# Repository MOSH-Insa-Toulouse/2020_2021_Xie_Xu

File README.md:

# 2020_2021- Qiang XU and Xiaotong XIE in 5ISS 

<div align=center></div>

Our class in SMART DEVICES

Contact : [Qiang XU](qxu@etud.insa-toulouse.fr)
          [Xiaotong XIE](x_xie@etud.insa-toulouse.fr)

- [x] Introduction the measurement chain and smart devices
- [x] Internship at AIME
- [x] TPs relating to the design of an analog circuit to interface the gas sensor produced to the AIME
- [x] TP on Git and the GitHub platform
- [x] TP on microcontrollers and open source hardware
- [x] TP on the production of electronic cards under KiCad
- [ ] Complete the whole project
---

## 2020_2021 5ISS KiCad

### Arduino Project

### KiCad - Shield for Arduino

#### TODO Concevoir une carte avec KiCad

- [x] Create project
- [x] Try to make the initial connection
- [x] Design the circuit board
- [x] Create original AIME components
- [x] Import 3D models
- [x] Complete package
- [x] Complete circuit wiring
- [ ] Solve the problem that the circuit board cannot display normally
- [x] Practice using Github
- [ ] Use Github proficiently

#### KiCad Tools used

[KiCad EDA - Schematic Capture & PCB Design Software](https://kicad-pcb.org/), version: 5.1.8

Open source EDA / electronics CAD software for Windows, macOS and Linux.

[Find 3D mod as you want!](https://grabcad.com/library)

If you want, you can place a tractor or Trump model on the circuit board

[Library of kicad](https://gitlab.com/kicad/libraries)

#### Librairies de composants

* LED_THT:LED_D5.0mm
* Resistor_THT:R_Axial_DIN0207_L6.3mm_D2.5mm_P10.16mm_Horizontal
* MyAIME:SIP-8
* Capacitor_THT:C_Radial_D4.0mm_H5.0mm_P1.50mm
* Package_DIP:DIP-8_W7.62mm
* MyAIME:TO-5-10_Window

#### Electrical diagram

## Component placement

## Routage

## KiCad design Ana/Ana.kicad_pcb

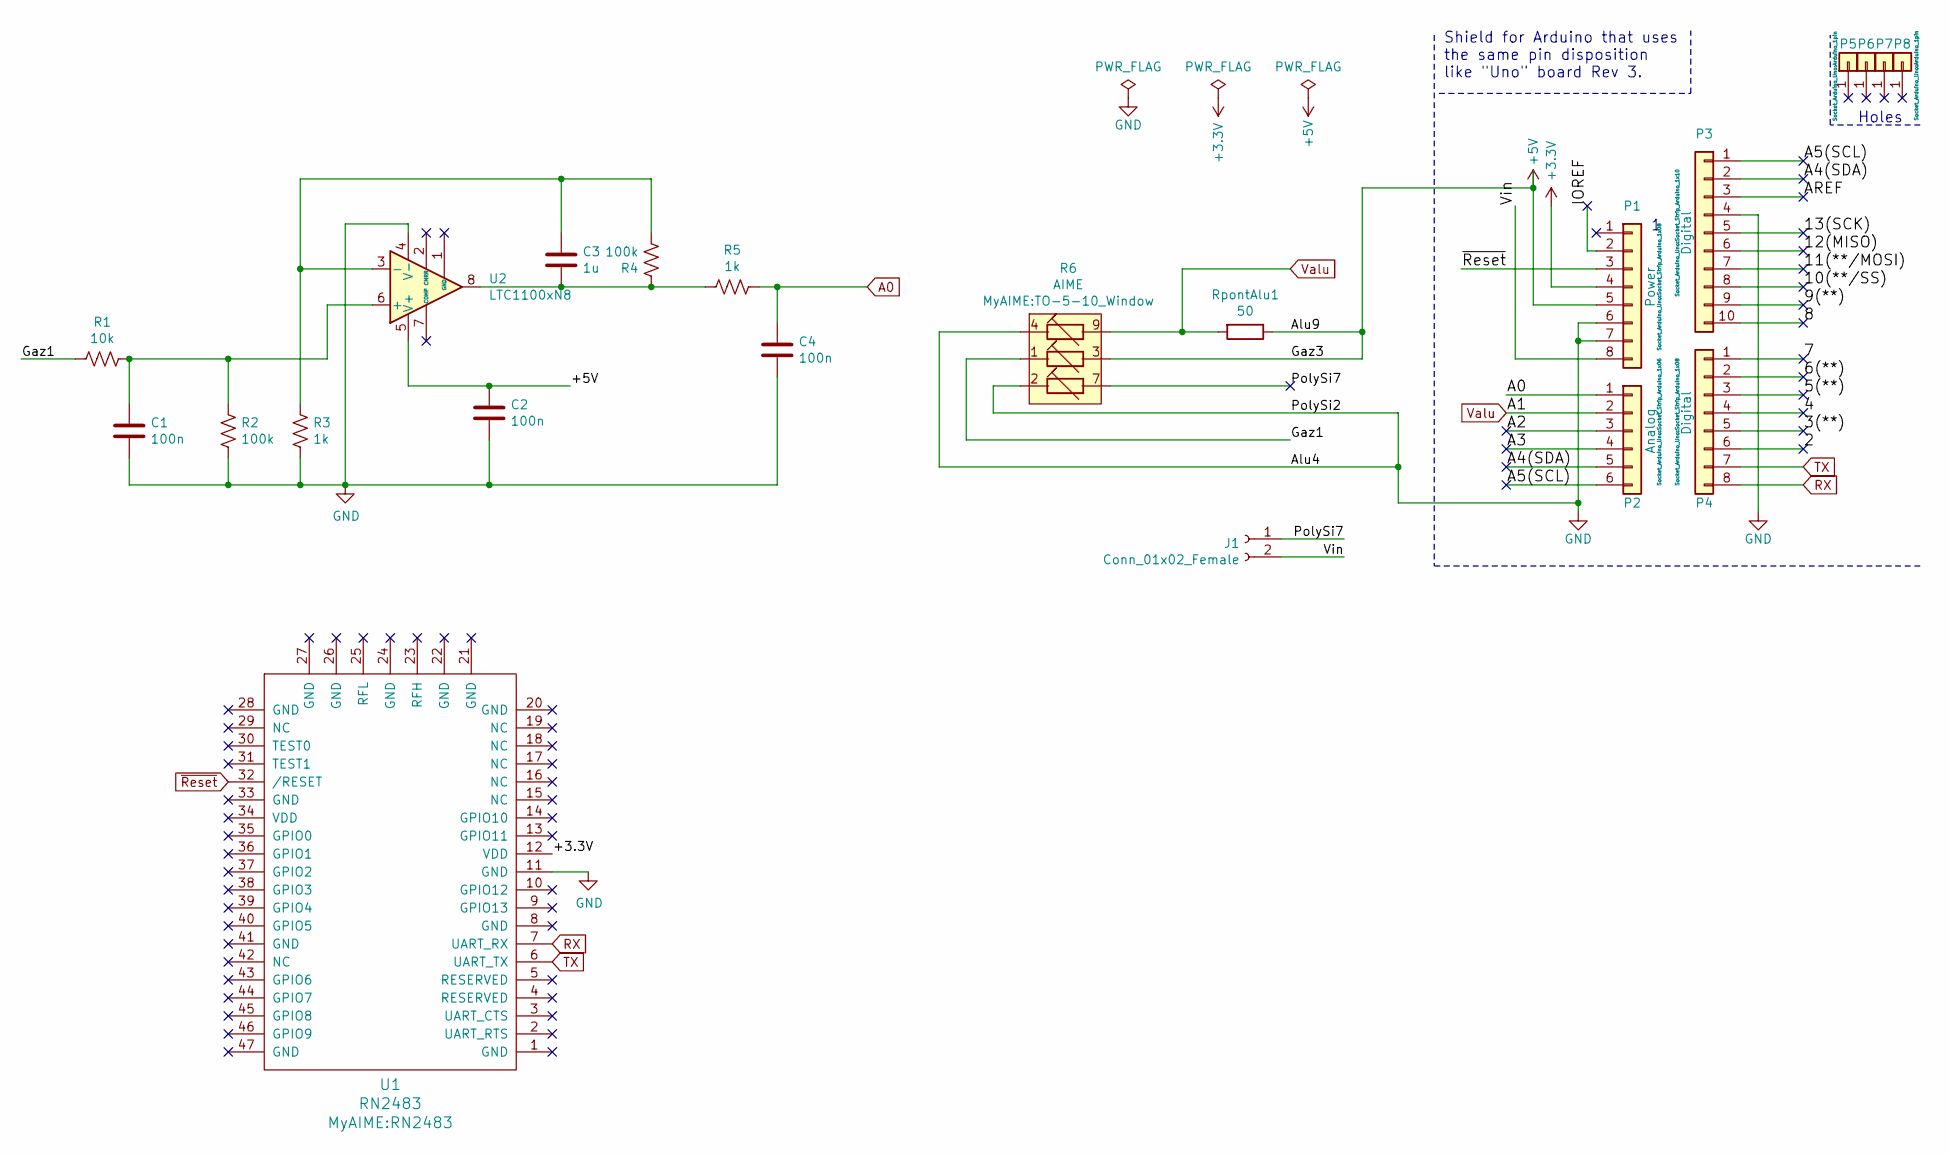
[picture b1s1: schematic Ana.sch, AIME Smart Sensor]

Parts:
C1, C2, C4: 100n; C_Radial_D4.0mm_H5.0mm_P1.50mm
C3: 1u; C_Radial_D4.0mm_H5.0mm_P1.50mm
J1: Conn_01x02_Female; PinSocket_1x02_P1.27mm_Vertical
P1: Power; Socket_Strip_Arduino_1x08
P2: Analog; Socket_Strip_Arduino_1x06
P3: Digital; Socket_Strip_Arduino_1x10
P4: Digital; Socket_Strip_Arduino_1x08
P5, P6, P7, P8: CONN_01X01; Arduino_1pin
R1: 10k; R_Axial_DIN0207_L6.3mm_D2.5mm_P10.16mm_Horizontal
R2, R4: 100k; R_Axial_DIN0207_L6.3mm_D2.5mm_P10.16mm_Horizontal
R3, R5: 1k; R_Axial_DIN0207_L6.3mm_D2.5mm_P10.16mm_Horizontal
R6: AIME; TO-5-10_Window
RpontAlu1: 50; R_Axial_DIN0207_L6.3mm_D2.5mm_P10.16mm_Horizontal
U1: RN2483
U2: LTC1100xN8; DIP-8_W7.62mm

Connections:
+3V3: P1.4
+5V: C2.1, P1.5, R6.3, RpontAlu1.1, U2.5 (V+)
/2: P4.6
/3(**): P4.5
/4: P4.4
/5(**): P4.3
/6(**): P4.2
/7: P4.1
/8: P3.10
/9(**): P3.9
/10(**/SS): P3.8
/11(**/MOSI): P3.7
/12(MISO): P3.6
/13(SCK): P3.5
/+3.3V: U1.12 (VDD)
/A2: P2.3
/A3: P2.4
/A4(SDA): P2.5, P3.2
/A5(SCL): P2.6, P3.1
/AREF: P3.3
/Gaz1: R1.1, R6.1
/IOREF: P1.2
/PolySi7: J1.1, R6.7
/Vin: J1.2, P1.8
A0: C4.1, P2.1, R5.1
GND: C1.2, C2.2, C4.2, P1.6, P1.7, P3.4, R2.1, R3.1, R6.2, R6.4, U1.11 (GND), U2.4 (V-)
unnamed: C1.1, R1.2, R2.2, U2.6 (+)
unnamed: C3.1, R3.2, R4.2, U2.3 (-)
unnamed: C3.2, R4.1, R5.2, U2.8
RX: P4.8, U1.7 (UART_RX)
TX: P4.7, U1.6 (UART_TX)
Valu: P2.2, R6.9, RpontAlu1.2
~Reset: P1.3, U1.32 (/RESET)

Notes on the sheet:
Holes
Shield for Arduino that uses the same pin disposition like "Uno" board Rev 3.

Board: 2 copper layers, 22 parts (0 on the bottom side), 15 nets, no tracks yet.

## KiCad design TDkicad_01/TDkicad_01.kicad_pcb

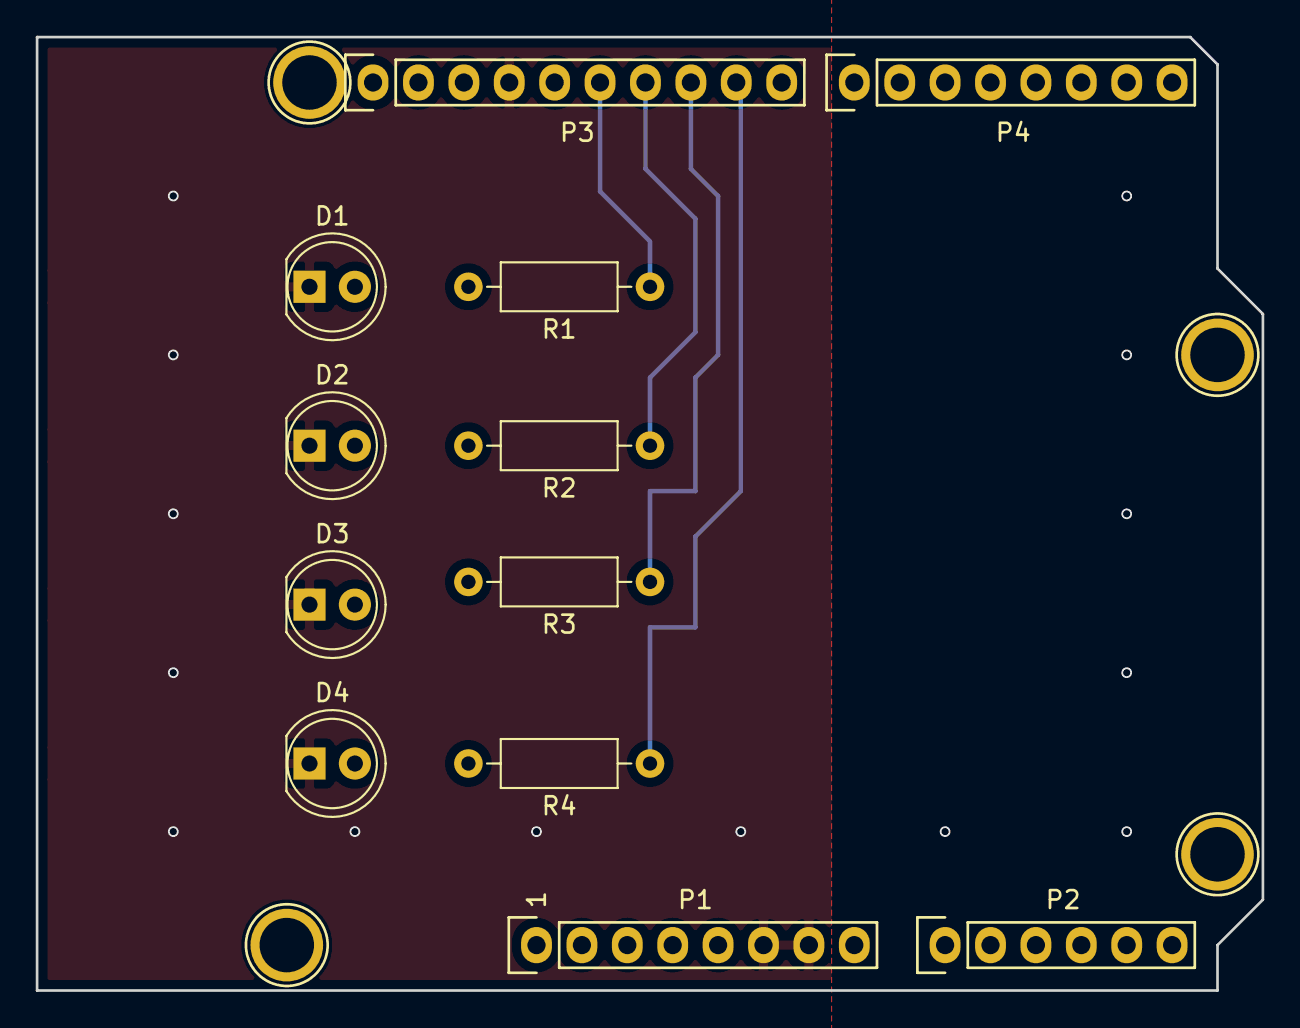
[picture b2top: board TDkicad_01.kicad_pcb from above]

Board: 2 copper layers, 68.6 x 53.3 mm, 16 parts (0 on the bottom side), 11 nets.

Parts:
D1, D2, D3, D4: LED; LED_D5.0mm
P1: Power; Socket_Strip_Arduino_1x08
P2: Analog; Socket_Strip_Arduino_1x06
P3: Digital; Socket_Strip_Arduino_1x10
P4: Digital; Socket_Strip_Arduino_1x08
P5, P6, P7, P8: CONN_01X01; Arduino_1pin
R1, R2, R3, R4: 470; R_Axial_DIN0207_L6.3mm_D2.5mm_P10.16mm_Horizontal

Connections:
/A4(SDA): P2.5, P3.2
/A5(SCL): P2.6, P3.1
/LED1: P3.6, R1.1
/LED2: P3.7, R2.1
/LED3: P3.8, R3.1
/LED4: P3.9, R4.1
GND: D1.1, D2.1, D3.1, D4.1, P1.6, P1.7, P3.4
unnamed: D1.2, R1.2
unnamed: D2.2, R2.2
unnamed: D3.2, R3.2
unnamed: D4.2, R4.2

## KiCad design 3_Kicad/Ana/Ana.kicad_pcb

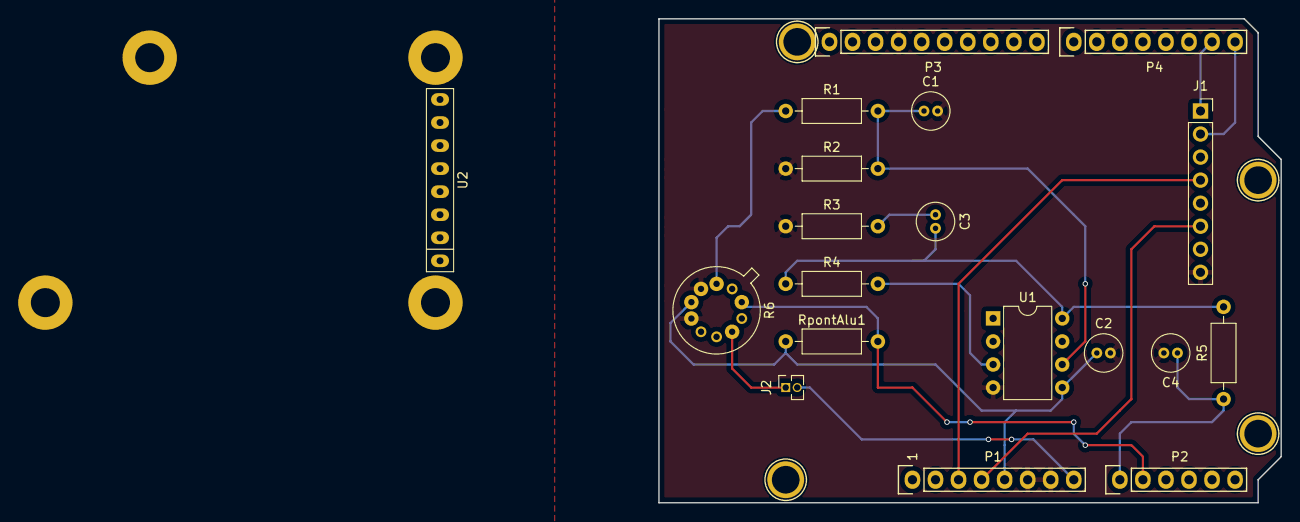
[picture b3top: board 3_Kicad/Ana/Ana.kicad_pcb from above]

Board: 2 copper layers, 68.6 x 53.3 mm, 23 parts (0 on the bottom side), 16 nets.

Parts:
C1, C2, C4: 100n; C_Radial_D4.0mm_H5.0mm_P1.50mm
C3: 1u; C_Radial_D4.0mm_H5.0mm_P1.50mm
J1: Conn_01x08_Female; PinSocket_1x08_P2.54mm_Vertical
J2: Conn_01x02_Female; PinSocket_1x02_P1.27mm_Vertical
P1: Power; Socket_Strip_Arduino_1x08
P2: Analog; Socket_Strip_Arduino_1x06
P3: Digital; Socket_Strip_Arduino_1x10
P4: Digital; Socket_Strip_Arduino_1x08
P5, P6, P7, P8: CONN_01X01; Arduino_1pin
R1: 10k; R_Axial_DIN0207_L6.3mm_D2.5mm_P10.16mm_Horizontal
R2, R4: 100k; R_Axial_DIN0207_L6.3mm_D2.5mm_P10.16mm_Horizontal
R3, R5: 1k; R_Axial_DIN0207_L6.3mm_D2.5mm_P10.16mm_Horizontal
R6: AIME; TO-5-10_Window
RpontAlu1: 50; R_Axial_DIN0207_L6.3mm_D2.5mm_P10.16mm_Horizontal
U1: LTC1100xN8; DIP-8_W7.62mm
U2: RN2483_Breakout; SIP-8

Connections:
+3V3: J1.6, P1.4
+5V: C2.1, P1.5, R6.3, RpontAlu1.1, U1.5
/A4(SDA): P2.5, P3.2
/A5(SCL): P2.6, P3.1
/Gaz1: R1.1, R6.1
/PolySi7: J2.1, R6.7
/Vin: J2.2, P1.8
A0: C4.1, P2.1, R5.1
GND: C1.2, C2.2, C4.2, J1.8, P1.6, P1.7, P3.4, R2.1, R3.1, R6.2, R6.4, U1.4
unnamed: C1.1, R1.2, R2.2, U1.6
unnamed: C3.1, R3.2, R4.2, U1.3
unnamed: C3.2, R4.1, R5.2, U1.8
RX: J1.2, P4.8
TX: J1.1, P4.7
Valu: P2.2, R6.9, RpontAlu1.2
~Reset: J1.4, P1.3

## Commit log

2020-12-07 led+resistor
2020-12-09 KiCad:Composant+Schematic
2020-12-09 Sensor+Filtre+RN2483
2020-12-09 Waiting for PCB layout
2020-12-10 Kicad Version2.0
2020-12-10 Add files and test. 测试能不能用中文。
2020-12-10 Add some explanatory documents
2020-12-10 test
2020-12-10 add logo
2021-01-15 Create a folder to describe each part.
2021-01-15 Create a folder to describe each part
